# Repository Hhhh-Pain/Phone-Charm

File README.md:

# Phone-Charm
First PCB Creation

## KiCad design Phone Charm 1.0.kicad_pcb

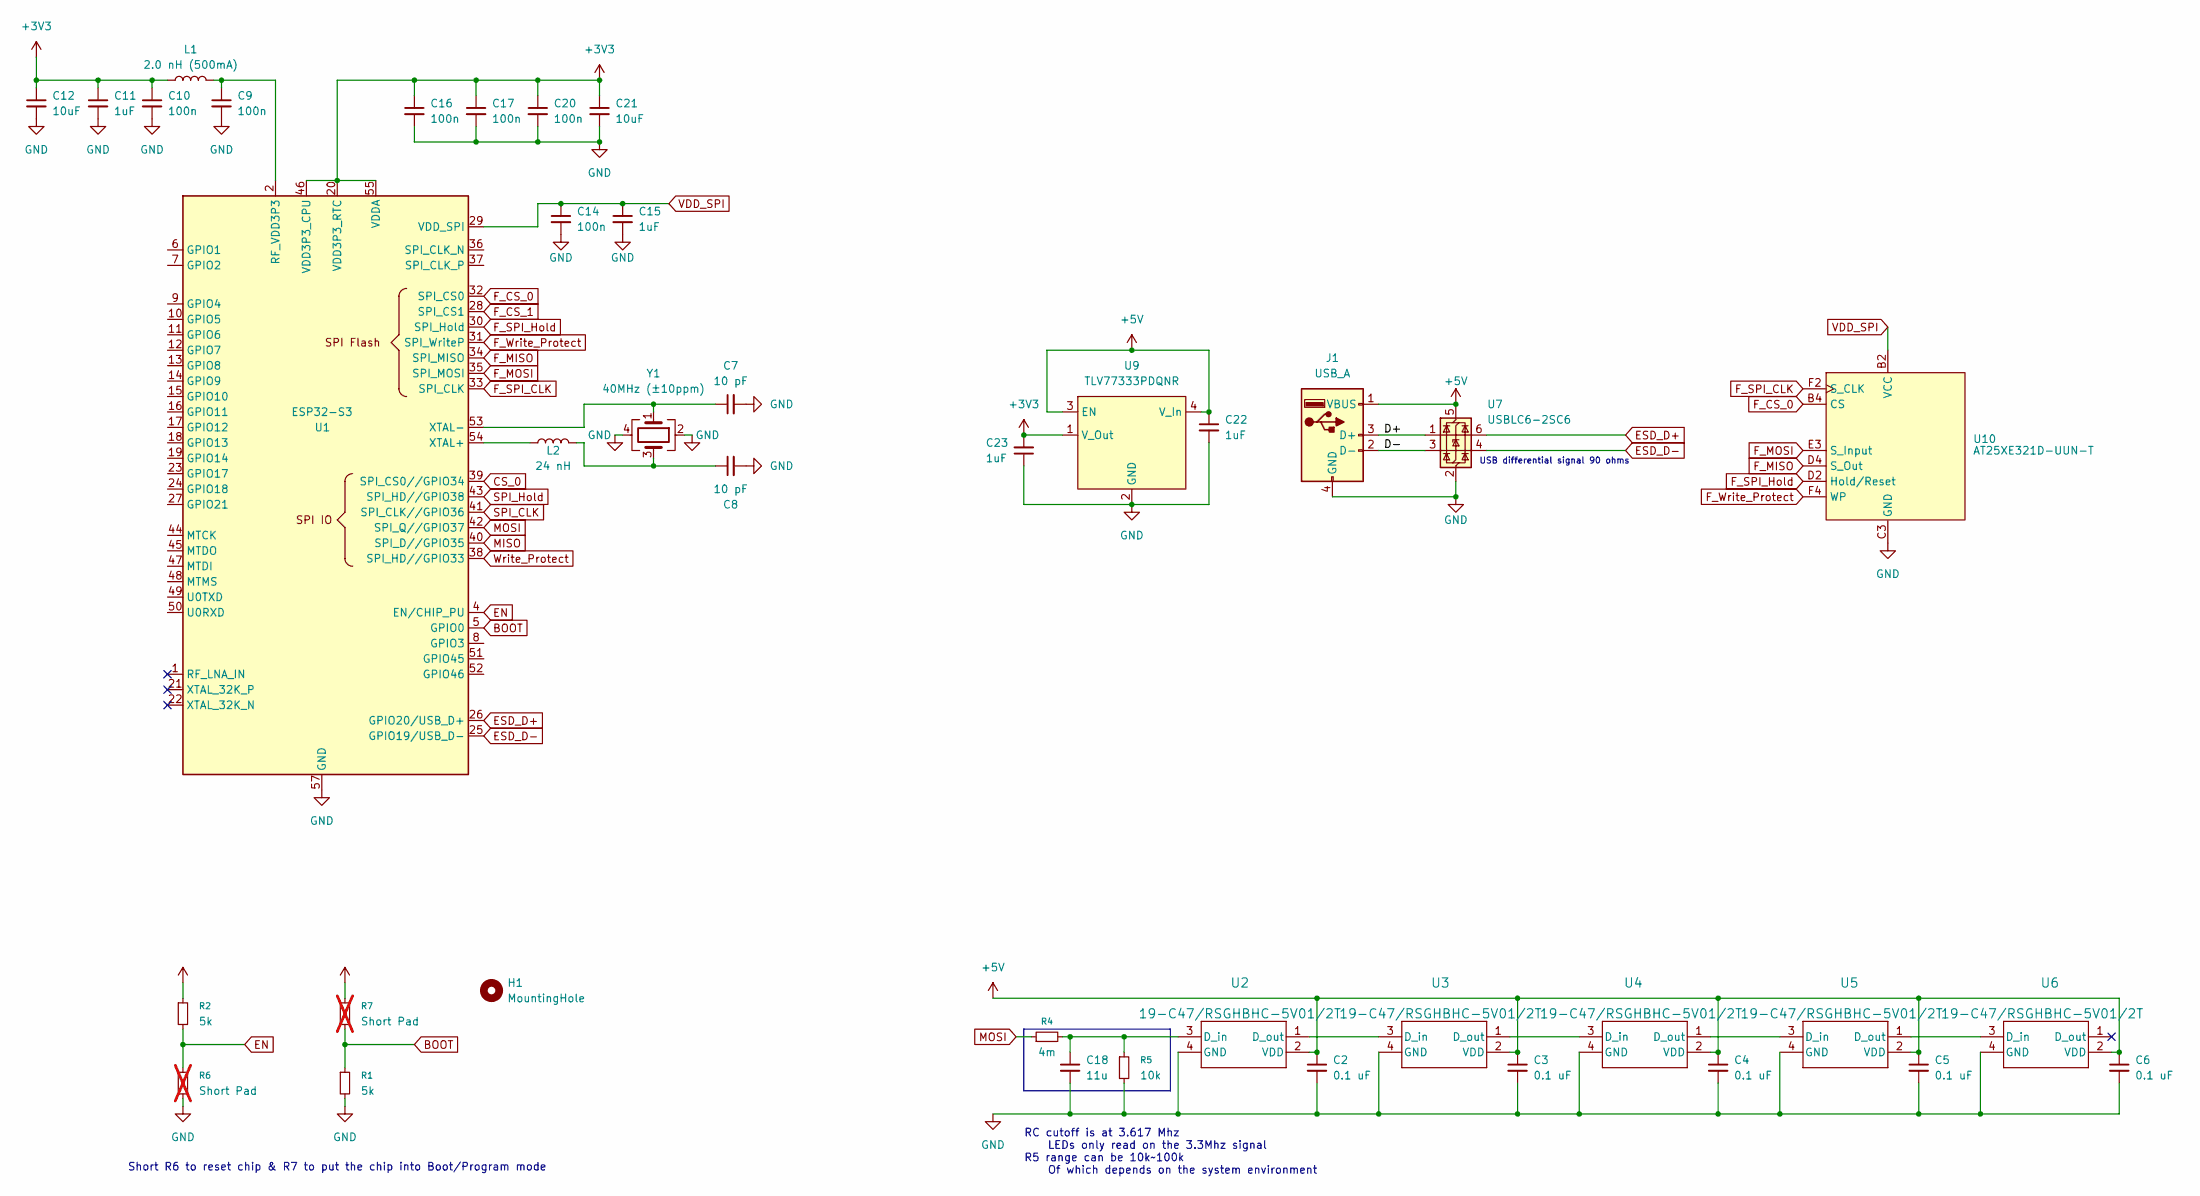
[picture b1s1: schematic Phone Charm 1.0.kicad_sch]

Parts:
C2, C3, C4, C5, C6: 0.1 uF; C_0201_0603Metric
C7, C8: 10 pF; C_0201_0603Metric
C9, C10, C14, C16, C17, C20: 100n; C_0201_0603Metric
C11, C15, C22, C23: 1uF; C_0201_0603Metric
C12, C21: 10uF; C_0201_0603Metric
C18: 11u; C_0201_0603Metric
H1: MountingHole; MountingHole_2.5mm_Pad_Via
J1: USB_A; usb-a-PCB
L1: 2.0 nH (500mA); L_0201_0603Metric
L2: 24 nH; L_0201_0603Metric
R1, R2: 5k; R_0201_0603Metric
R4: 4m; R_0201_0603Metric
R5: 10k; R_0201_0603Metric
R6, R7: Short Pad; R_0201_0603Metric; not fitted
U1: ESP32-S3; QFN-56-1EP_7x7mm_P0.4mm_EP4x4mm_1
U2, U3, U4, U5, U6: 19-C47/RSGHBHC-5V01/2T; 19-C47&slash_RSGHBHC-5V01&slash_2T_EVE
U7: USBLC6-2SC6; SOT-666
U9: TLV77333PDQNR; SUP_TPS3831L30DQNR
U10: AT25XE321D-UUN-T
Y1: 40MHz (±10ppm); XTAL_FW400WFMR1; Part Number FW400WFMR1DKR-ND or FW400WFMR1CT-ND

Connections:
+3V3: C10.1, C11.1, C12.1, C16.1, C17.1, C20.1, C21.1, C23.2, L1.1, R2.1, R7.1, U1.20 (VDD3P3_RTC), U1.46 (VDD3P3_CPU), U1.55 (VDDA), U1.56 (VDDA), U9.1 (V_Out)
+5V: C2.1, C3.1, C4.1, C5.1, C6.1, C22.1, J1.1 (VBUS), U2.2 (VDD), U3.2 (VDD), U4.2 (VDD), U5.2 (VDD), U6.2 (VDD), U7.5 (VBUS), U9.3 (EN), U9.4 (V_In)
/Microcontroller/D+: J1.3 (D+), U7.1 (I/O1)
/Microcontroller/D-: J1.2 (D-), U7.3 (I/O2)
BOOT: R1.1, R7.2, U1.5 (GPIO0)
CS_0: U1.39 (SPI_CS0//GPIO34)
EN: R2.2, R6.1, U1.4 (EN/CHIP_PU); also elsewhere on the board
ESD_D+: U1.26 (GPIO20/USB_D+), U7.6 (I/O1)
ESD_D-: U1.25 (GPIO19/USB_D-), U7.4 (I/O2)
F_CS_0: U1.32 (SPI_CS0), U10.B4 (CS)
F_CS_1: U1.28 (SPI_CS1)
F_MISO: U1.34 (SPI_MISO), U10.D4 (S_Out)
F_MOSI: U1.35 (SPI_MOSI), U10.E3 (S_Input)
F_SPI_CLK: U1.33 (SPI_CLK), U10.F2 (S_CLK)
F_SPI_Hold: U1.30 (SPI_Hold), U10.D2 (Hold/Reset)
F_Write_Protect: U1.31 (SPI_WriteP), U10.F4 (WP)
GND: C2.2, C3.2, C4.2, C5.2, C6.2, C7.2, C8.2, C9.2, C10.2, C11.2, C12.2, C14.2, C15.2, C16.2, C17.2, C18.2, C20.2, C21.2, C22.2, C23.1, J1.4 (GND), R1.2, R5.2, R6.2, U1.57 (GND), U2.4 (GND), U3.4 (GND), U4.4 (GND), U5.4 (GND), U6.4 (GND), U7.2 (GND), U9.2 (GND), U9.5 (GND), U10.C3 (GND), Y1.2, Y1.4; also elsewhere on the board
MISO: U1.40 (SPI_D//GPIO35)
MOSI: R4.1, U1.42 (SPI_Q//GPIO37)
unnamed: C8.1, L2.2, Y1.3
unnamed: C9.1, L1.2, U1.2 (RF_VDD3P3), U1.3 (RF_VDD3P3)
unnamed: L2.1, U1.54 (XTAL+)
unnamed: C7.1, U1.53 (XTAL-), Y1.1
unnamed: C18.1, R4.2, R5.1, U2.3 (D_in)
unnamed: U2.1 (D_out), U3.3 (D_in)
unnamed: U3.1 (D_out), U4.3 (D_in)
unnamed: U4.1 (D_out), U5.3 (D_in)
unnamed: U5.1 (D_out), U6.3 (D_in)
SPI_CLK: U1.41 (SPI_CLK//GPIO36)
SPI_Hold: U1.43 (SPI_HD//GPIO38)
VDD_SPI: C14.1, C15.1, U1.29 (VDD_SPI), U10.B2 (VCC)
Write_Protect: U1.38 (SPI_HD//GPIO33)

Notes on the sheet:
RC cutoff is at 3.617 Mhz LEDs only read on the 3.3Mhz signal R5 range can be 10k~100k Of which depends on the system environment
USB differential signal 90 ohms
Short R6 to reset chip & R7 to put the chip into Boot/Program mode

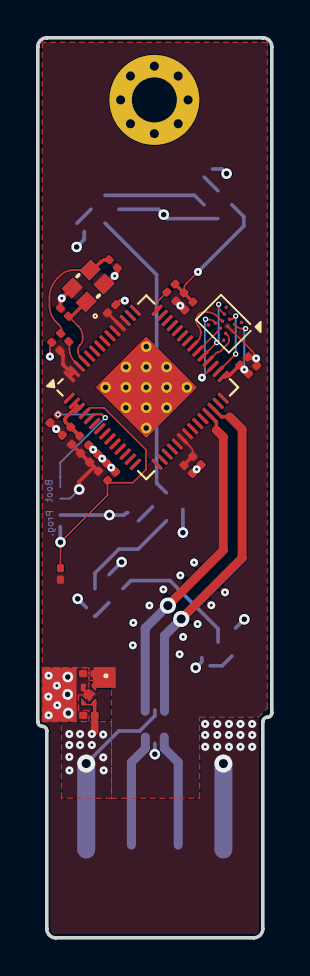
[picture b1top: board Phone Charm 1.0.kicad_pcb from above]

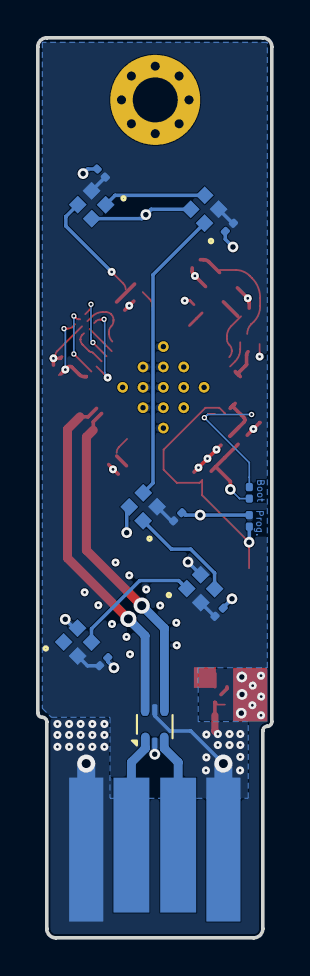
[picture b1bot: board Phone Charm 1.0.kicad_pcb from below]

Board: 4 copper layers, 13.0 x 50.0 mm, 41 parts (14 on the bottom side), 26 nets.

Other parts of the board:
C13: 10uF; C_0201_0603Metric

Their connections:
EN: C13.1; also elsewhere on the board
GND: C13.2; also elsewhere on the board

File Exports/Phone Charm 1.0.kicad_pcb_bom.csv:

Designator,Quantity,Value,Footprint,Package,MPN,DNP,Mount_Type,Description
"C10, C14, C16, C17, C20, C9",6,100n,C_0201_0603Metric,,,,smt,"Unpolarized capacitor, small symbol"
"C11, C15, C22, C23",4,1uF,C_0201_0603Metric,,,,smt,"Unpolarized capacitor, small symbol"
"C12, C13, C21",3,10uF,C_0201_0603Metric,,,,smt,"Unpolarized capacitor, small symbol"
C18,1,11u,C_0201_0603Metric,,,,smt,"Unpolarized capacitor, small symbol"
"C2, C3, C4, C5, C6",5,0.1 uF,C_0201_0603Metric,,,,smt,"Unpolarized capacitor, small symbol"
"C7, C8",2,10 pF,C_0201_0603Metric,,,,smt,"Unpolarized capacitor, small symbol"
J1,1,USB_A,usb-a-PCB,,,,tht,USB Type A connector
L1,1,2.0 nH (500mA),L_0201_0603Metric,,,,smt,Inductor
L2,1,24 nH,L_0201_0603Metric,,,,smt,Inductor
"R1, R2",2,5k,R_0201_0603Metric,,,,smt,"Resistor, small symbol"
R4,1,4m,R_0201_0603Metric,,,,smt,"Resistor, small symbol"
R5,1,10k,R_0201_0603Metric,,,,smt,"Resistor, small symbol"
R6,1,Short Pad,R_0201_0603Metric,,,Yes,smt,"Resistor, small symbol"
R7,1,Short Pad,R_0201_0603Metric,,,Yes,smt,"Resistor, small symbol"
U1,1,ESP32-S3,QFN-56-1EP_7x7mm_P0.4mm_EP4x4mm_1,,,,smt,"Microcontroller, Wi-Fi 802.11b/g/n, Bluetooth, 32bit"
U10,1,AT25XE321D-UUN-T,AT25XE321D-UUN-T,,,,smt,32-Mbit serial peripheral interface (SPI) Flash memory
"U2, U3, U4, U5, U6",5,19-C47/RSGHBHC-5V01/2T,19-C47&slash_RSGHBHC-5V01&slash_2T_EVE,,,,smt,
U7,1,USBLC6-2SC6,SOT-666,,,,smt,"Very low capacitance ESD protection diode, 2 data-line, SOT-23-6"
U9,1,TLV77333PDQNR,SUP_TPS3831L30DQNR,,,,smt,"TLV773 300mA, Small-Size, High-PSRR, Low-Dropout Regulator"
Y1,1,40MHz (±10ppm),XTAL_FW400WFMR1,,FW400WFMR1DKR-ND or FW400WFMR1CT-ND ,,smt,"Four pin crystal, GND on pins 2 and 3"
